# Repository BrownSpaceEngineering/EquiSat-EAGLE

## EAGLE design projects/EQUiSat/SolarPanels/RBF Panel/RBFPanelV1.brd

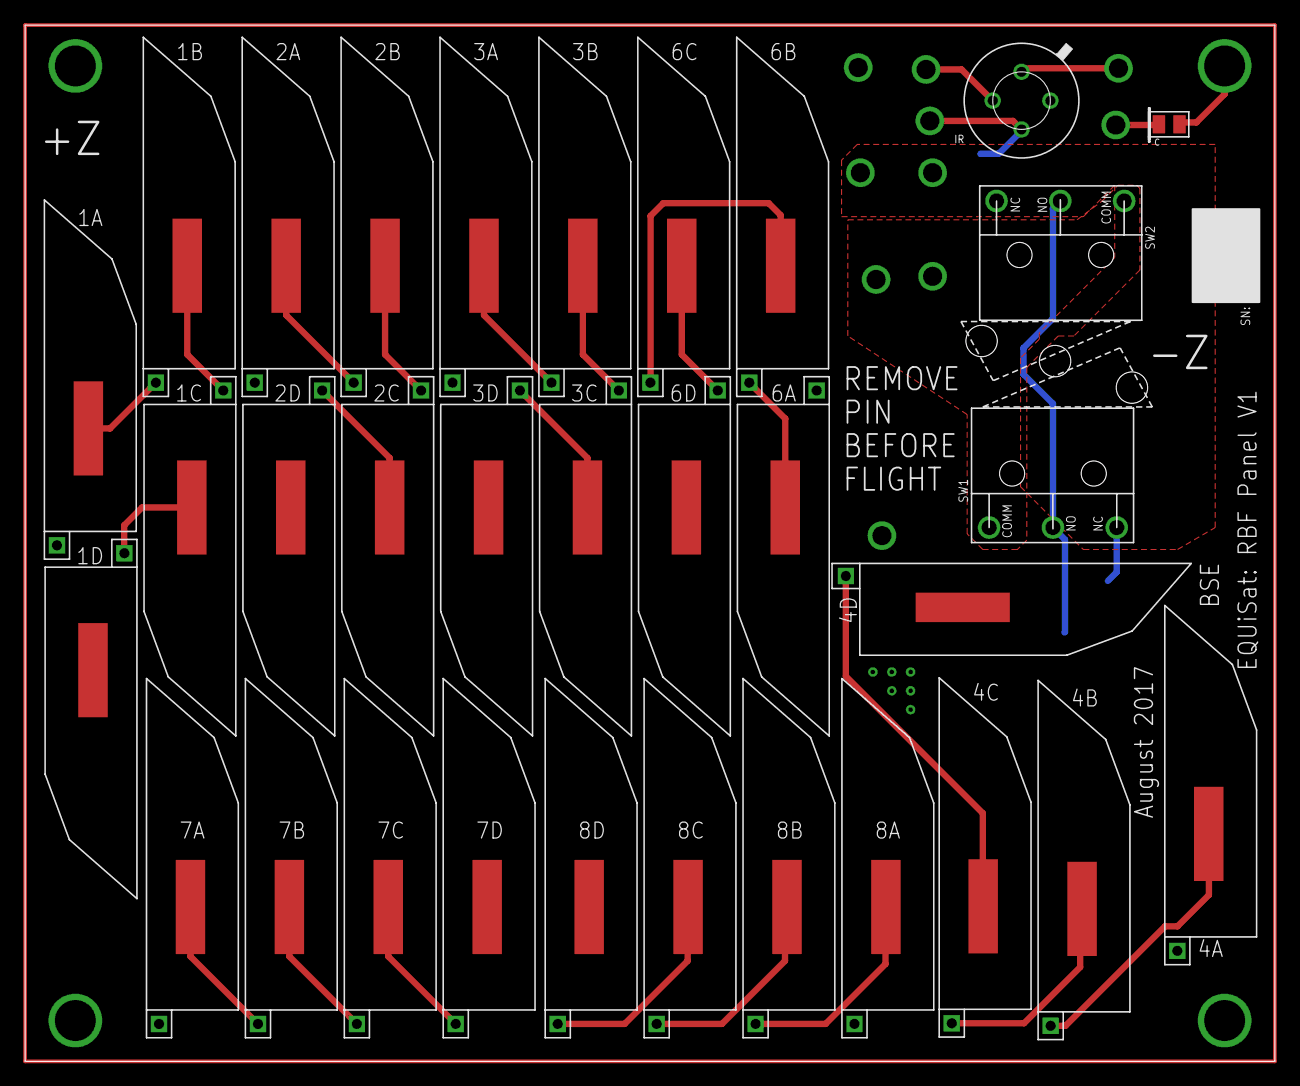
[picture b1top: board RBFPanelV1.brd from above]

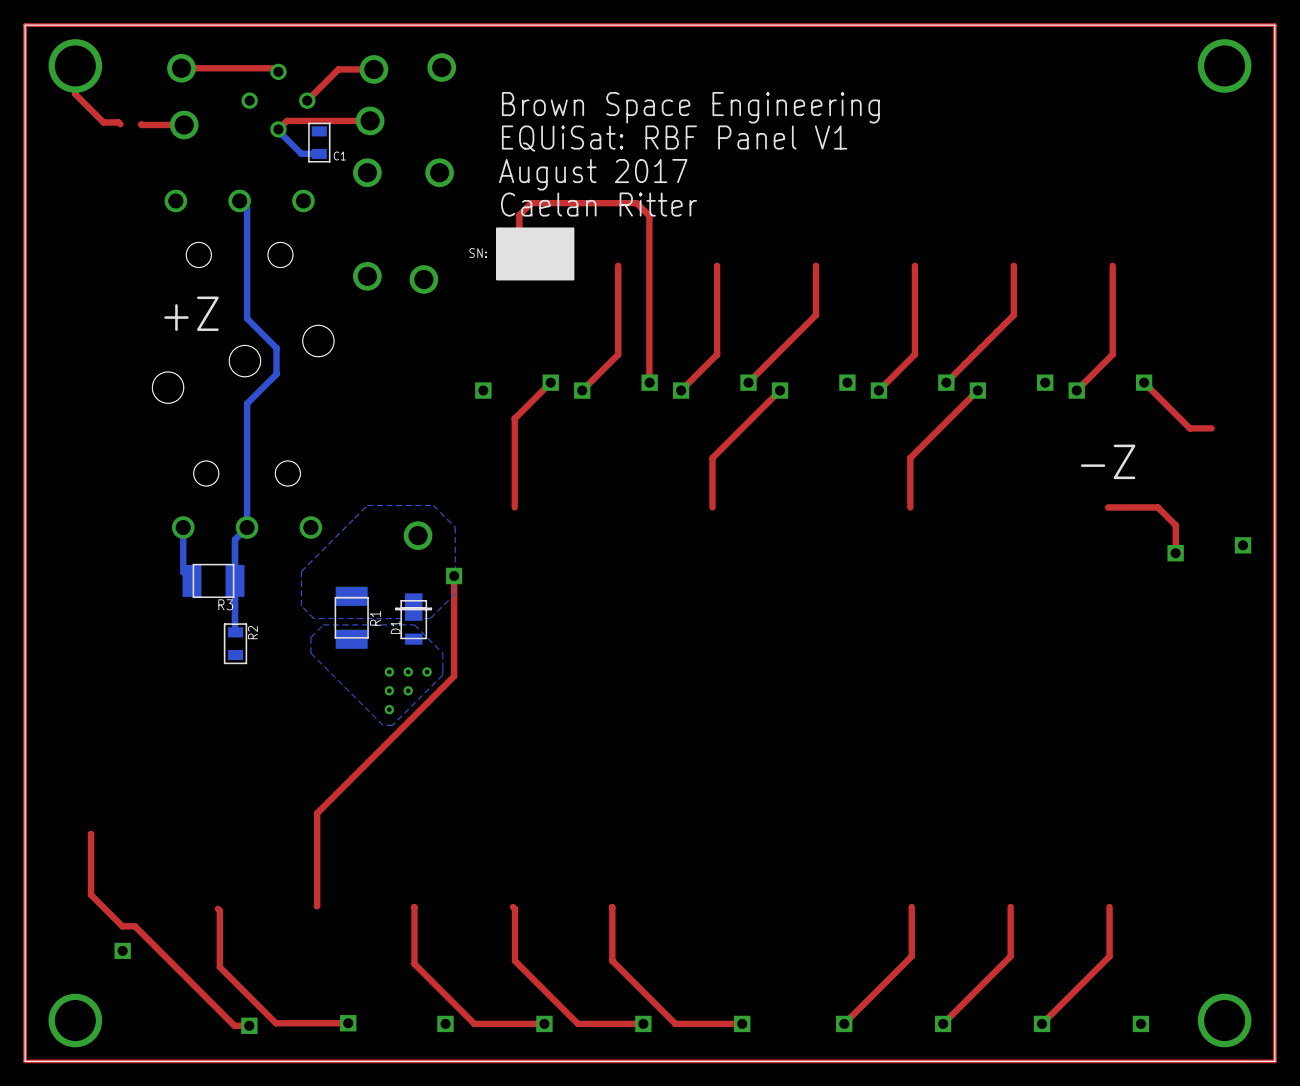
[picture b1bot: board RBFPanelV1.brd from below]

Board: 2 copper layers, 99.5 x 82.5 mm, 47 parts (5 on the bottom side), 31 nets.

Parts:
1A, 1B, 1C, 1D, 2A, 2B, 2C, 2D, 3A, 3B, 3C, 3D, 4A, 4B, 4C, 4D, 6A, 6B, 6C, 6D, 7A, 7B, 7C, 7D, 8A, 8B, 8C, 8D: SOLARCELLV3; TRISOLX-V3
3V3: 3V3; VIA-60MIL
C1: 0.1uF; 0805
D1: DFLS130L; PWRDI-123
GND: GND; VIA-60MIL
IR: MXL90620
PD: PHOTODETECTOR; PHOTODECTORDEVICE2
PD-OUT: PD-OUT; VIA-60MIL
PWR-OUT: SP-PWR-OUT; VIA-60MIL
R1, R3: 0R; 1210
R2: 10M; 0805
SCL: SCL; VIA-60MIL
SDA: SDA; VIA-60MIL
SW1, SW2: D2F-L-A
V1, V2: LION-IN; VIA-60MIL
V3, V4: LION-OUT; VIA-60MIL

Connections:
3V3: 3V3.P$1, C1.2, IR.VDD
GND: 1A.ANODE, 2A.ANODE, 3A.ANODE, 4A.ANODE, 6A.ANODE, 7A.ANODE, 8A.ANODE, C1.1, GND.P$1, IR.VSS, PD.A, R2.2
LION-IN: SW1.P$1, SW2.P$1, V1.P$1, V2.P$1
LION-OUT: R3.P$2, SW1.P$3, SW2.P$3, V3.P$1, V4.P$1
unnamed: 2C.CATHODE, 2D.ANODE
unnamed: 1C.CATHODE, 1D.ANODE
unnamed: 1B.CATHODE, 1C.ANODE
unnamed: 1A.CATHODE, 1B.ANODE
unnamed: 2B.CATHODE, 2C.ANODE
unnamed: 2A.CATHODE, 2B.ANODE
unnamed: 3C.CATHODE, 3D.ANODE
unnamed: 3B.CATHODE, 3C.ANODE
unnamed: 3A.CATHODE, 3B.ANODE
unnamed: 4C.CATHODE, 4D.ANODE
unnamed: 4B.CATHODE, 4C.ANODE
unnamed: 4A.CATHODE, 4B.ANODE
unnamed: R2.1, R3.P$1, SW1.P$2, SW2.P$2
unnamed: 6C.CATHODE, 6D.ANODE
unnamed: 6B.CATHODE, 6C.ANODE
unnamed: 6A.CATHODE, 6B.ANODE
unnamed: 7C.CATHODE, 7D.ANODE
unnamed: 7B.CATHODE, 7C.ANODE
unnamed: 7A.CATHODE, 7B.ANODE
unnamed: 8C.CATHODE, 8D.ANODE
unnamed: 8B.CATHODE, 8C.ANODE
unnamed: 8A.CATHODE, 8B.ANODE
PD-OUT: PD.C, PD-OUT.P$1
SCL: IR.SCL, SCL.P$1
SDA: IR.SDA, SDA.P$1
SP-PWR: 1D.CATHODE, 2D.CATHODE, 3D.CATHODE, 4D.CATHODE, 6D.CATHODE, 7D.CATHODE, 8D.CATHODE, D1.A, R1.P$1
SP-PWR-OUT: D1.C, PWR-OUT.P$1, R1.P$2

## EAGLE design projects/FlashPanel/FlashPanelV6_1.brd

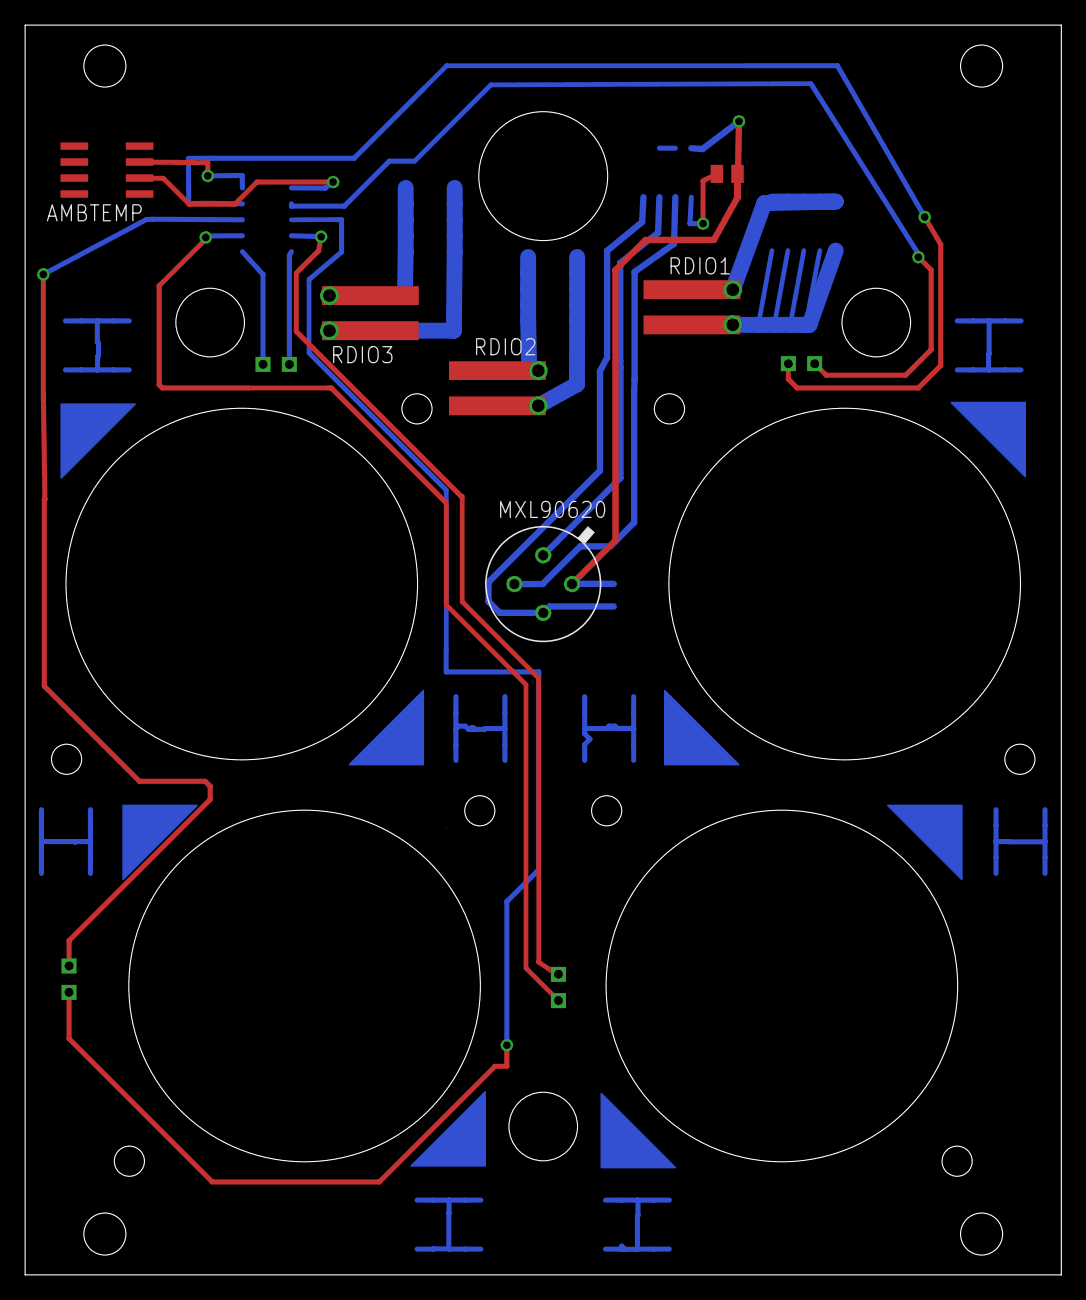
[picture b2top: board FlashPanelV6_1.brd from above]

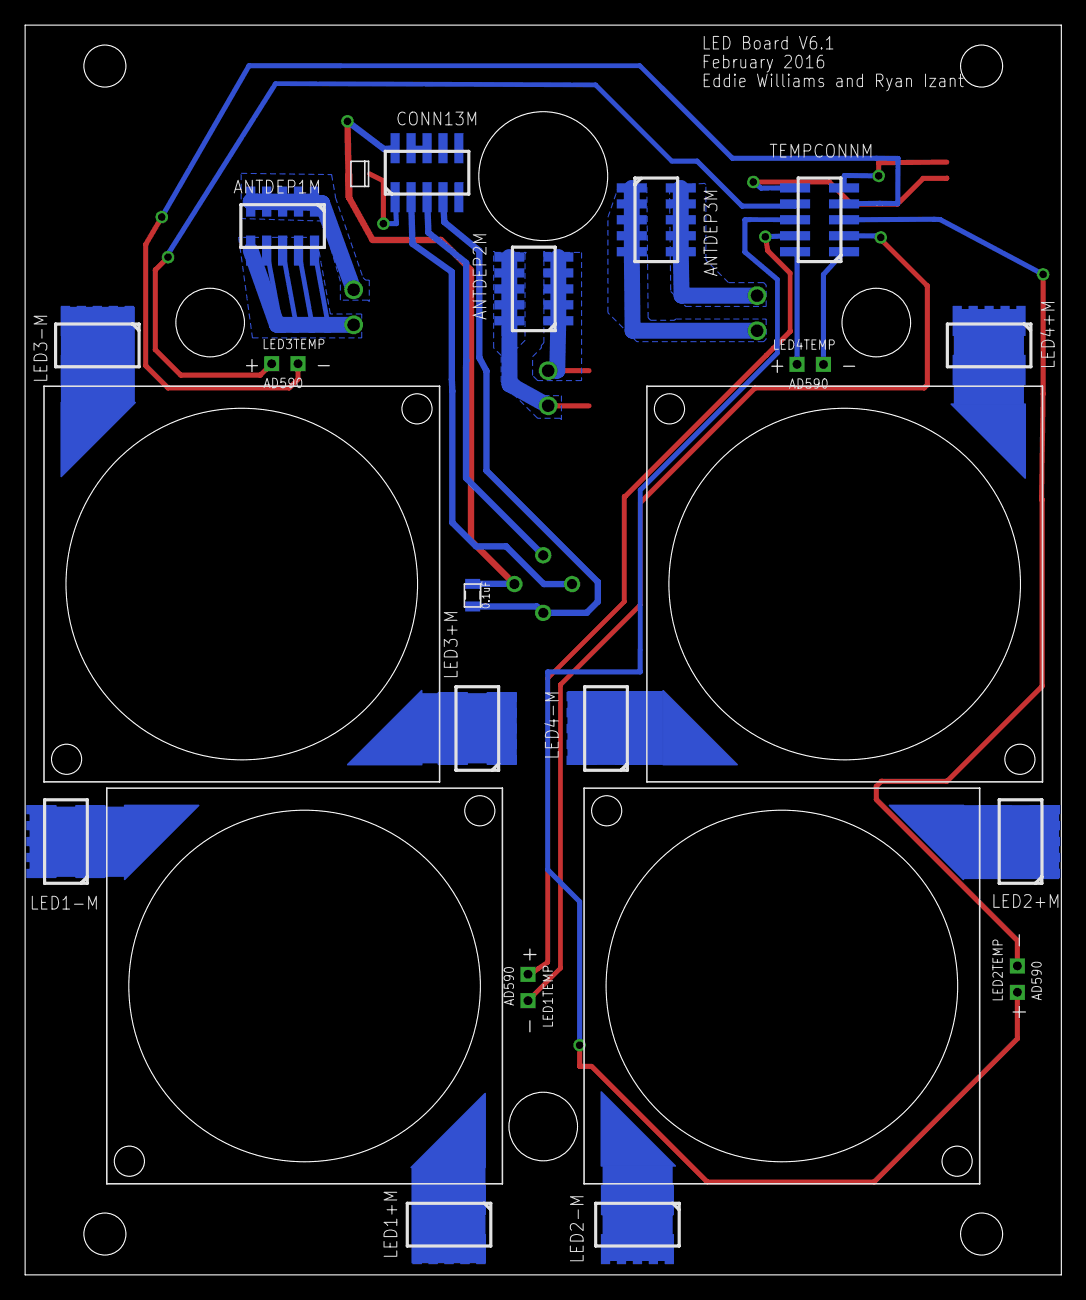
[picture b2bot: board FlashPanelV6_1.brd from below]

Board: 2 copper layers, 82.5 x 99.5 mm, 28 parts (26 on the bottom side), 30 nets.

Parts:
AMBTEMP: AD590; 8SOIC
ANTDEP1M, ANTDEP2M, ANTDEP3M: 10PINMALE
C1: 0.1uF; 0805
CONN13M: 10PINMALE
LED1, LED2, LED3, LED4: CXM27
LED1+M, LED1-M, LED2+M, LED2-M, LED3+M, LED3-M, LED4+M, LED4-M: 10PINMALE
LED1TEMP, LED2TEMP, LED3TEMP, LED4TEMP: AD590-TH; AD590TH
RDIO1, RDIO2, RDIO3: RDIO; RDIO_DPLY
TEMPCONNM: 10PINMALE
U$1: MXL90620
U$2: PHOTODETECTBOTTOM

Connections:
3V3: C1.2, CONN13M.P4, U$1.VDD
GND: C1.1, CONN13M.P10, U$1.VSS, U$2.GND
unnamed: LED3.ANODE, LED3+M.P1, LED3+M.P2, LED3+M.P3, LED3+M.P4, LED3+M.P5, LED3+M.P6, LED3+M.P7, LED3+M.P8, LED3+M.P9, LED3+M.P10
unnamed: LED3.CATHODE, LED3-M.P1, LED3-M.P2, LED3-M.P3, LED3-M.P4, LED3-M.P5, LED3-M.P6, LED3-M.P7, LED3-M.P8, LED3-M.P9, LED3-M.P10
unnamed: LED2.CATHODE, LED2+M.P1, LED2+M.P2, LED2+M.P3, LED2+M.P4, LED2+M.P5, LED2+M.P6, LED2+M.P7, LED2+M.P8, LED2+M.P9, LED2+M.P10
unnamed: LED2.ANODE, LED2-M.P1, LED2-M.P2, LED2-M.P3, LED2-M.P4, LED2-M.P5, LED2-M.P6, LED2-M.P7, LED2-M.P8, LED2-M.P9, LED2-M.P10
unnamed: LED1.CATHODE, LED1+M.P1, LED1+M.P2, LED1+M.P3, LED1+M.P4, LED1+M.P5, LED1+M.P6, LED1+M.P7, LED1+M.P8, LED1+M.P9, LED1+M.P10
unnamed: LED1.ANODE, LED1-M.P1, LED1-M.P2, LED1-M.P3, LED1-M.P4, LED1-M.P5, LED1-M.P6, LED1-M.P7, LED1-M.P8, LED1-M.P9, LED1-M.P10
unnamed: LED4.CATHODE, LED4-M.P1, LED4-M.P2, LED4-M.P3, LED4-M.P4, LED4-M.P5, LED4-M.P6, LED4-M.P7, LED4-M.P8, LED4-M.P9, LED4-M.P10
unnamed: LED4.ANODE, LED4+M.P1, LED4+M.P2, LED4+M.P3, LED4+M.P4, LED4+M.P5, LED4+M.P6, LED4+M.P7, LED4+M.P8, LED4+M.P9, LED4+M.P10
unnamed: ANTDEP1M.P1, ANTDEP1M.P2, ANTDEP1M.P3, ANTDEP1M.P4, ANTDEP1M.P5, RDIO1.P3, RDIO1.P4
unnamed: ANTDEP2M.P6, ANTDEP2M.P7, ANTDEP2M.P8, ANTDEP2M.P9, ANTDEP2M.P10, RDIO2.P1, RDIO2.P2
unnamed: ANTDEP2M.P1, ANTDEP2M.P2, ANTDEP2M.P3, ANTDEP2M.P4, ANTDEP2M.P5, RDIO2.P3, RDIO2.P4
unnamed: ANTDEP3M.P6, ANTDEP3M.P7, ANTDEP3M.P8, ANTDEP3M.P9, ANTDEP3M.P10, RDIO3.P1, RDIO3.P2
unnamed: ANTDEP3M.P1, ANTDEP3M.P2, ANTDEP3M.P3, ANTDEP3M.P4, ANTDEP3M.P5, RDIO3.P3, RDIO3.P4
unnamed: LED4TEMP.P$2, TEMPCONNM.P1
unnamed: LED1TEMP.P$2, TEMPCONNM.P2
unnamed: LED2TEMP.P$2, TEMPCONNM.P3
unnamed: LED3TEMP.P$2, TEMPCONNM.P4
unnamed: LED4TEMP.P$1, TEMPCONNM.P10
unnamed: LED1TEMP.P$1, TEMPCONNM.P9
unnamed: LED2TEMP.P$1, TEMPCONNM.P8
unnamed: LED3TEMP.P$1, TEMPCONNM.P7
unnamed: AMBTEMP.3, TEMPCONNM.P5
unnamed: AMBTEMP.2, TEMPCONNM.P6
PDOUT: CONN13M.P1, U$2.PWROUT
RDIO1: ANTDEP1M.P6, ANTDEP1M.P7, ANTDEP1M.P8, ANTDEP1M.P9, ANTDEP1M.P10, RDIO1.P1, RDIO1.P2
SCL: CONN13M.P3, U$1.SCL
SDA: CONN13M.P2, U$1.SDA
TEST: CONN13M.P8, CONN13M.P9

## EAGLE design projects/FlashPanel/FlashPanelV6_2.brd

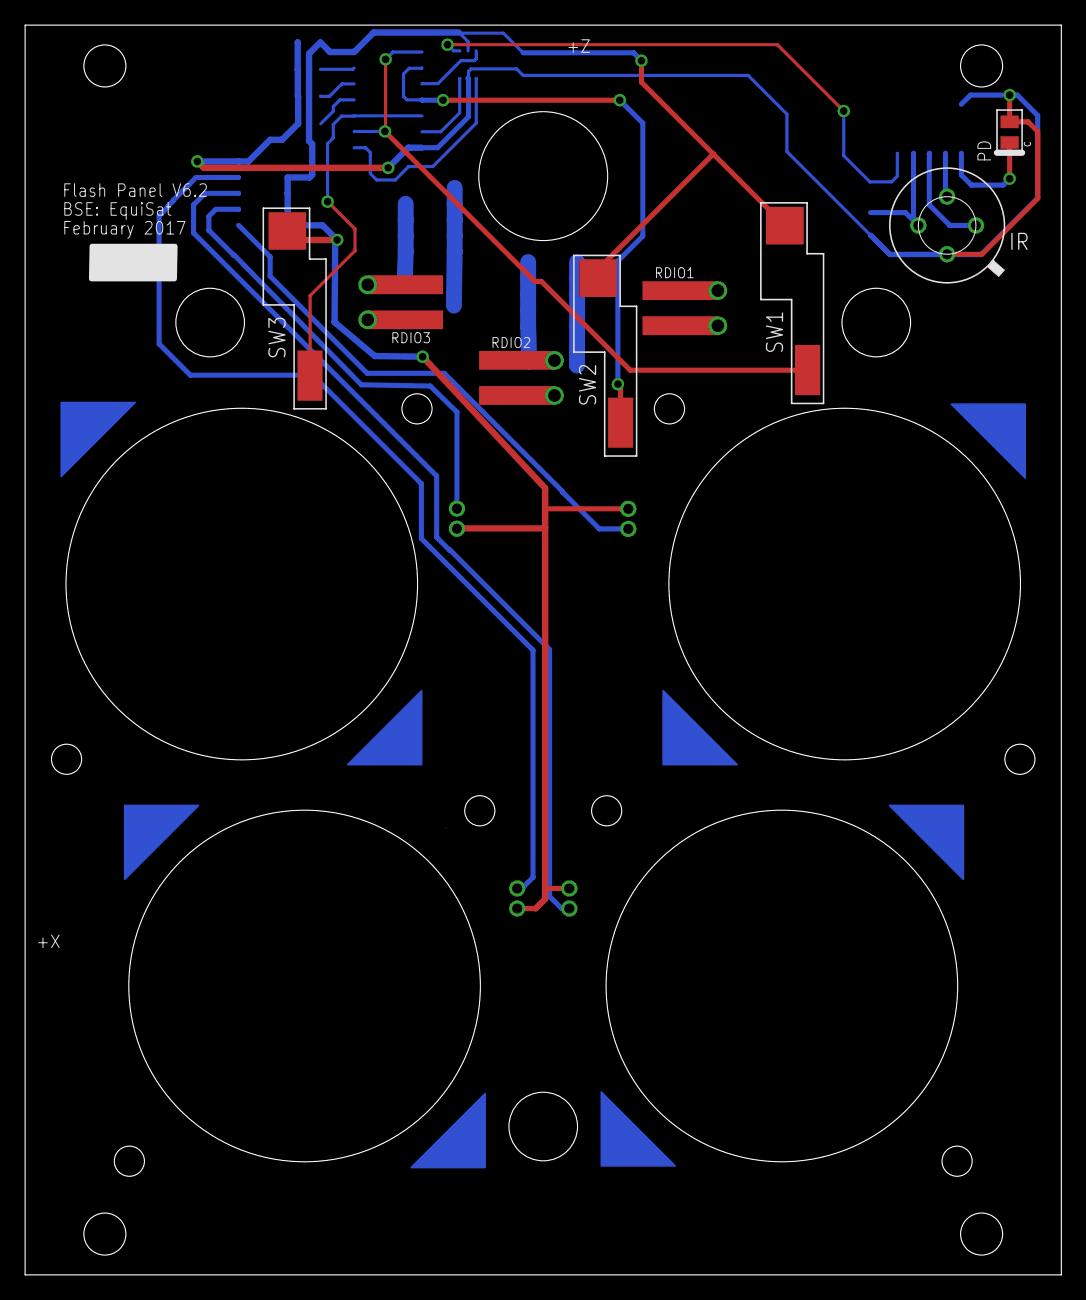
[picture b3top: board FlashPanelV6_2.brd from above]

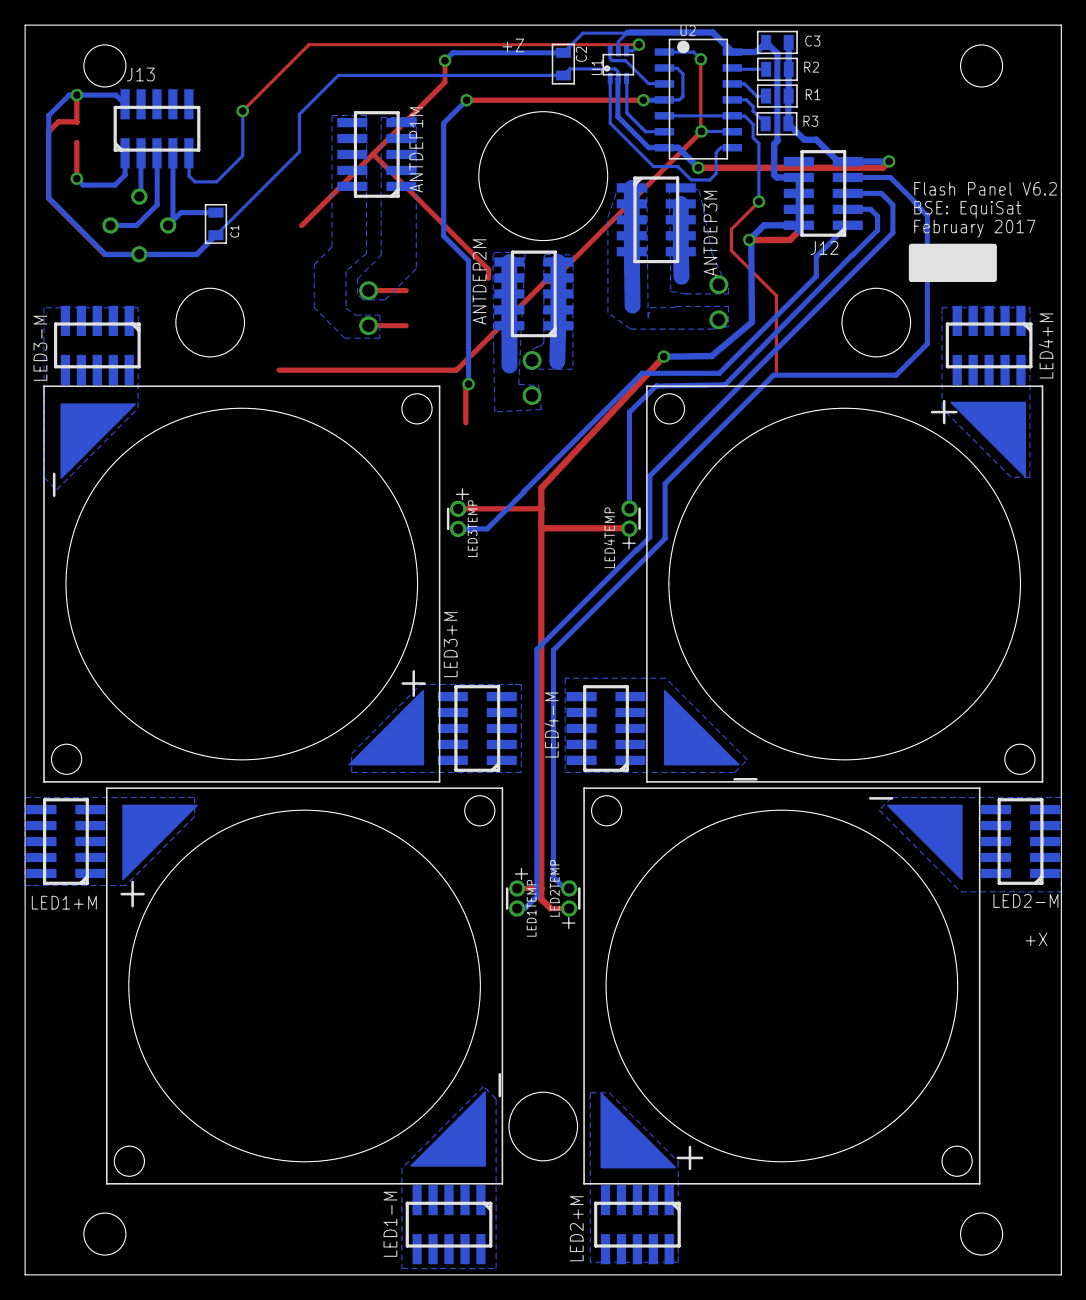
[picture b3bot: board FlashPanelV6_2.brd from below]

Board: 2 copper layers, 82.5 x 99.5 mm, 37 parts (25 on the bottom side), 34 nets.

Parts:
ANTDEP1M, ANTDEP2M, ANTDEP3M: 10PINMALE
C1, C2, C3: 0.1uF; 0805
IR: MXL90614; MXL90620
J12, J13: 10PINMALE
LED1, LED2, LED3, LED4: CXM27
LED1+M, LED1-M, LED2+M, LED2-M, LED3+M, LED3-M, LED4+M, LED4-M: 10PINMALE
LED1TEMP, LED2TEMP, LED3TEMP, LED4TEMP: AD590FLATPACK; FLATPACK
PD: TEMD6200
R1, R2, R3: 10K; 0805
RDIO1, RDIO2, RDIO3: RDIO; RDIO_DPLY
SW1, SW2, SW3: SW-DETECT; SW-SPRING
U1: SN74LVC1G332; DCK-6
U2: CD74HC08M96; SOIC-14

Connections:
5V: C2.1, C3.1, J12.P7, J12.P8, J12.P9, J12.P10, LED1TEMP.+, LED2TEMP.+, LED3TEMP.+, LED4TEMP.+, SW1.P$1, SW2.P$1, SW3.P$1, U1.P$5, U2.P$14
DET_RTN: J13.P5, U1.P$4
GND: C1.1, C2.2, C3.2, IR.VSS, J12.P5, J13.P10, PD.A, R1.1, R2.1, R3.1, U1.P$2, U2.P$7
IRVDD: C1.2, IR.VDD, J13.P4
LED1M: LED1.CATHODE, LED1-M.P1, LED1-M.P2, LED1-M.P3, LED1-M.P4, LED1-M.P5, LED1-M.P6, LED1-M.P7, LED1-M.P8, LED1-M.P9, LED1-M.P10
LED1P: LED1.ANODE, LED1+M.P1, LED1+M.P2, LED1+M.P3, LED1+M.P4, LED1+M.P5, LED1+M.P6, LED1+M.P7, LED1+M.P8, LED1+M.P9, LED1+M.P10
LED1TEMP-: J12.P3, LED1TEMP.-
LED2M: LED2.CATHODE, LED2-M.P1, LED2-M.P2, LED2-M.P3, LED2-M.P4, LED2-M.P5, LED2-M.P6, LED2-M.P7, LED2-M.P8, LED2-M.P9, LED2-M.P10
LED2P: LED2.ANODE, LED2+M.P1, LED2+M.P2, LED2+M.P3, LED2+M.P4, LED2+M.P5, LED2+M.P6, LED2+M.P7, LED2+M.P8, LED2+M.P9, LED2+M.P10
LED2TEMP-: J12.P4, LED2TEMP.-
LED3M: LED3.CATHODE, LED3-M.P1, LED3-M.P2, LED3-M.P3, LED3-M.P4, LED3-M.P5, LED3-M.P6, LED3-M.P7, LED3-M.P8, LED3-M.P9, LED3-M.P10
LED3P: LED3.ANODE, LED3+M.P1, LED3+M.P2, LED3+M.P3, LED3+M.P4, LED3+M.P5, LED3+M.P6, LED3+M.P7, LED3+M.P8, LED3+M.P9, LED3+M.P10
LED3TEMP-: J12.P1, LED3TEMP.-
LED4M: LED4.CATHODE, LED4-M.P1, LED4-M.P2, LED4-M.P3, LED4-M.P4, LED4-M.P5, LED4-M.P6, LED4-M.P7, LED4-M.P8, LED4-M.P9, LED4-M.P10
LED4P: LED4.ANODE, LED4+M.P1, LED4+M.P2, LED4+M.P3, LED4+M.P4, LED4+M.P5, LED4+M.P6, LED4+M.P7, LED4+M.P8, LED4+M.P9, LED4+M.P10
LED4TEMP-: J12.P2, LED4TEMP.-
unnamed: U1.P$6, U2.P$3
unnamed: U1.P$3, U2.P$6
unnamed: U1.P$1, U2.P$8
unnamed: SW1.P$2, U2.P$1, U2.P$9
unnamed: SW2.P$2, U2.P$2, U2.P$4
unnamed: SW3.P$2, U2.P$5, U2.P$10
unnamed: R2.2, U2.P$13
unnamed: R1.2, U2.P$12
unnamed: R3.2, U2.P$11
PDOUT: J13.P1, PD.C
RDIO1+: ANTDEP1M.P6, ANTDEP1M.P7, ANTDEP1M.P8, ANTDEP1M.P9, ANTDEP1M.P10, RDIO1.P3, RDIO1.P4
RDIO1-: ANTDEP1M.P1, ANTDEP1M.P2, ANTDEP1M.P3, ANTDEP1M.P4, ANTDEP1M.P5, RDIO1.P1, RDIO1.P2
RDIO2+: ANTDEP2M.P6, ANTDEP2M.P7, ANTDEP2M.P8, ANTDEP2M.P9, ANTDEP2M.P10, RDIO2.P3, RDIO2.P4
RDIO2-: ANTDEP2M.P1, ANTDEP2M.P2, ANTDEP2M.P3, ANTDEP2M.P4, ANTDEP2M.P5, RDIO2.P1, RDIO2.P2
RDIO3+: ANTDEP3M.P6, ANTDEP3M.P7, ANTDEP3M.P8, ANTDEP3M.P9, ANTDEP3M.P10, RDIO3.P3, RDIO3.P4
RDIO3-: ANTDEP3M.P1, ANTDEP3M.P2, ANTDEP3M.P3, ANTDEP3M.P4, ANTDEP3M.P5, RDIO3.P1, RDIO3.P2
SCL: IR.SCL, J13.P3
SDA: IR.SDA, J13.P2

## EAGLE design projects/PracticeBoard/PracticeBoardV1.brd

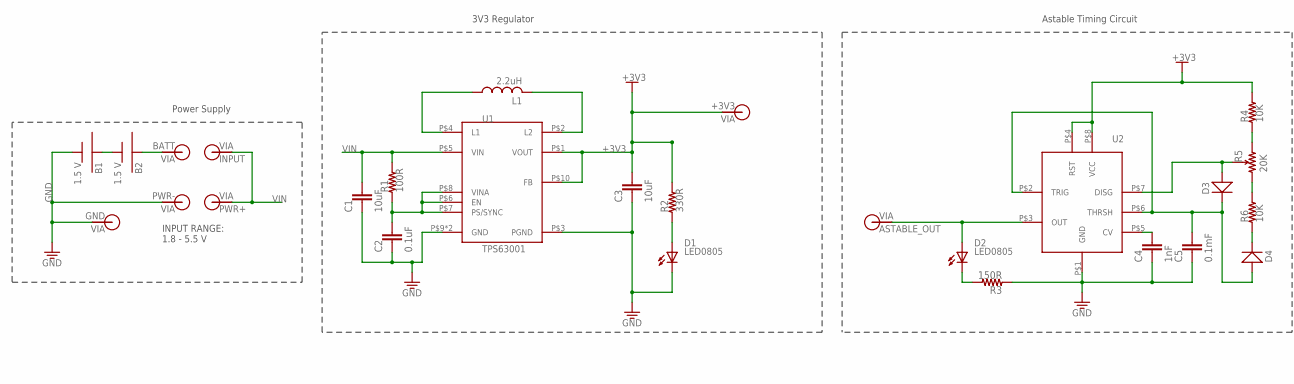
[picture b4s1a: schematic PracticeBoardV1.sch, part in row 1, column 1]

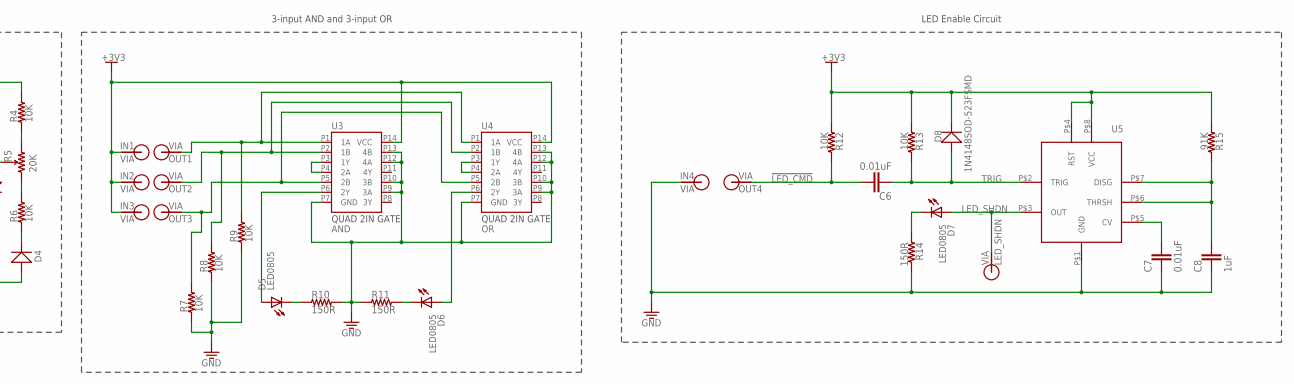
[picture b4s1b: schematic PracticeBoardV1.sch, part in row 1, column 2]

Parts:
B1, B2: 1.5 V; BCAAPC-BATT-HOLDER
C1, C3: 10uF; 0805
C2: 0.1uF; 0805
C4: 1nF; 0805
C5: 0.1mF; 0805
C6, C7: 0.01uF; 0805
C8: 1uF; 0805
D1, D2, D5, D6, D7: LED0805; 0805-D
D3, D4: 1N4148THRU-HOLE; 1N4148
D8: 1N4148SOD-523FSMD; SOD-523F
L1: 2.2uH; L3225M
R1: 100R; 0805
R2: 330R; 0805
R3, R10, R11, R14: 150R; 0805
R4, R6, R7, R8, R9, R12, R13: 10K; 0805
R5: 20K; P160KN
R15: 91K; 0805
U1: TPS63001; QFN10_POWERPAD
U2, U5: TLC555; SO-8
U3: AND; VQFN-14
U4: OR; TSSOP-14
V1: BATT; VIA-60MIL-SQ
V2: PWR-; VIA-60MIL-SQ
V3: INPUT; VIA-60MIL-SQ
V4: PWR+; VIA-60MIL-SQ
V5: +3V3; VIA-60MIL-SQ
V6: ASTABLE_OUT; VIA-60MIL-SQ
V7: IN1; VIA-60MIL-SQ
V8: IN2; VIA-60MIL-SQ
V9: IN3; VIA-60MIL-SQ
V10: OUT1; VIA-60MIL-SQ
V11: OUT2; VIA-60MIL-SQ
V12: OUT3; VIA-60MIL-SQ
V13: IN4; VIA-60MIL-SQ
V14: OUT4; VIA-60MIL-SQ
V15: LED_SHDN; VIA-60MIL-SQ
V16: GND; VIA-60MIL-SQ

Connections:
!LED_CMD!: C6.1, R12.2, V14.P$1
+3V3: C3.1, D8.C, R2.2, R4.2, R12.1, R13.1, R15.1, U1.P$1 (VOUT), U1.P$10 (FB), U2.P$4 (RST), U2.P$8 (VCC), U3.P14 (VCC), U4.P14 (VCC), U5.P$4 (RST), U5.P$8 (VCC), V5.P$1, V7.P$1, V8.P$1, V9.P$1
ASTABLE_OUT: D2.A, U2.P$3 (OUT), V6.P$1
GND: B1.MINUS, C1.2, C2.2, C3.2, C4.2, C5.2, C7.2, C8.2, D1.C, R3.1, R7.1, R8.1, R9.1, R10.2, R11.1, R14.2, U1.P$3 (PGND), U1.P$9 (GND), U1.PAD (GND), U2.P$1 (GND), U3.P7 (GND), U3.P9 (3A), U3.P10 (3B), U3.P12 (4A), U3.P13 (4B), U4.P7 (GND), U4.P9 (3A), U4.P10 (3B), U4.P12 (4A), U4.P13 (4B), U5.P$1 (GND), V2.P$1, V13.P$1, V16.P$1
LED_SHDN: D7.A, U5.P$3 (OUT), V15.P$1
unnamed: B1.PLUS, B2.MINUS
unnamed: C4.1, U2.P$5 (CV)
unnamed: C5.1, D3.C, D4.A, U2.P$2 (TRIG), U2.P$6 (THRSH)
unnamed: D5.C, R10.1
unnamed: L1.1, U1.P$4 (L1)
unnamed: L1.2, U1.P$2 (L2)
unnamed: R4.1, R5.P2 (2)
unnamed: D6.C, R11.2
unnamed: C2.1, R1.1, U1.P$6 (EN), U1.P$7 (PS/SYNC), U1.P$8 (VINA)
unnamed: R9.2, U3.P1 (1A), U4.P1 (1A), V10.P$1
unnamed: R8.2, U3.P2 (1B), U4.P2 (1B), V11.P$1
unnamed: R7.2, U3.P5 (2B), U4.P5 (2B), V12.P$1
unnamed: U4.P3 (1Y), U4.P4 (2A)
unnamed: U3.P3 (1Y), U3.P4 (2A)
unnamed: B2.PLUS, V1.P$1
unnamed: D3.A, R5.P3, U2.P$7 (DISG)
unnamed: R5.P1 (1), R6.2
unnamed: D7.C, R14.1
unnamed: C8.1, R15.2, U5.P$6 (THRSH), U5.P$7 (DISG)
unnamed: D5.A, U3.P6 (2Y)
unnamed: D2.C, R3.2
unnamed: C7.1, U5.P$5 (CV)
unnamed: D6.A, U4.P6 (2Y)
unnamed: D4.C, R6.1
unnamed: D1.A, R2.1
TRIG: C6.2, D8.A, R13.2, U5.P$2 (TRIG)
VIN: C1.1, R1.2, U1.P$5 (VIN), V3.P$1, V4.P$1

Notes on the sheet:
3V3 Regulator
Astable Timing Circuit
3-input AND and 3-input OR
LED Enable Circuit
Power Supply
INPUT RANGE: 1.8 - 5.5 V

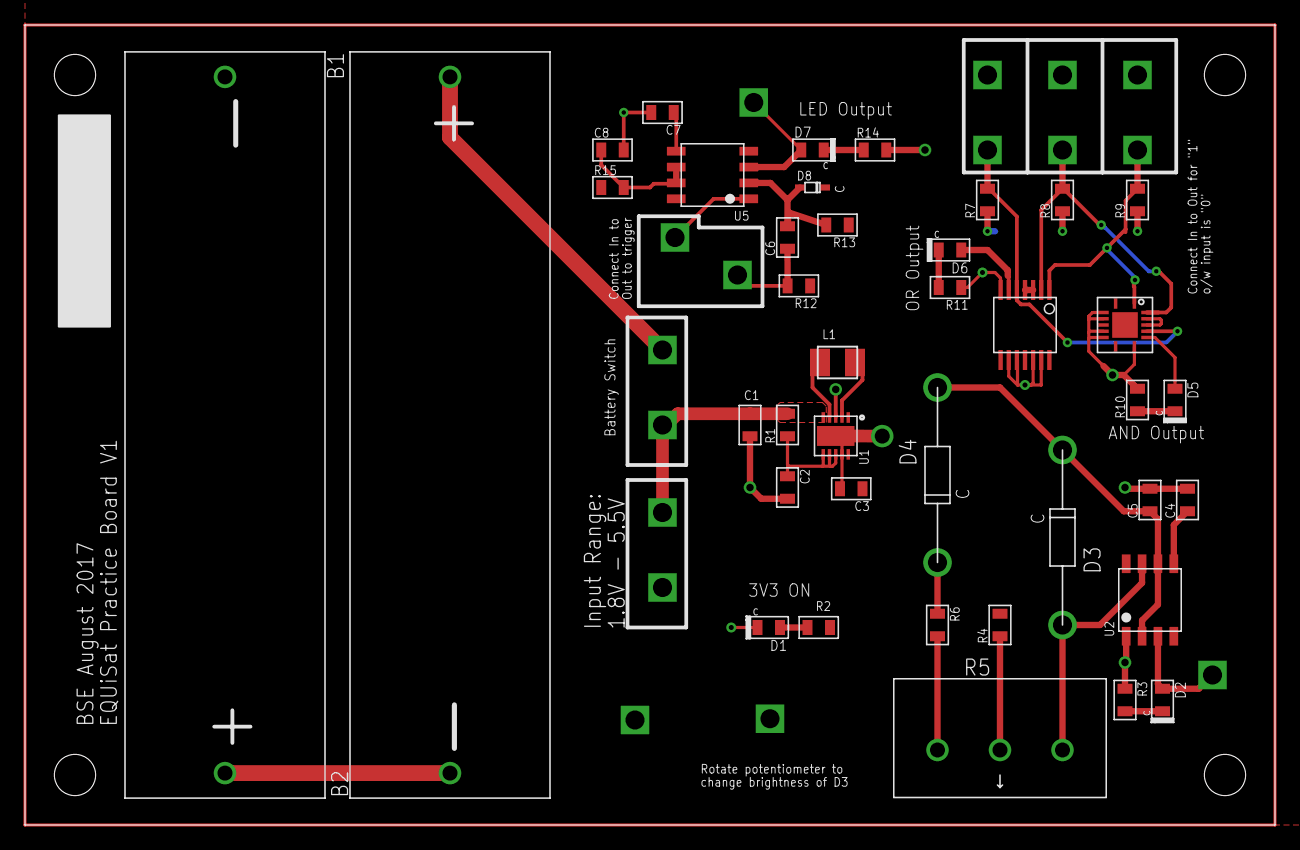
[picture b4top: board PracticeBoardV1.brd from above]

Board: 2 copper layers, 100.0 x 64.0 mm, 55 parts (0 on the bottom side), 32 nets.

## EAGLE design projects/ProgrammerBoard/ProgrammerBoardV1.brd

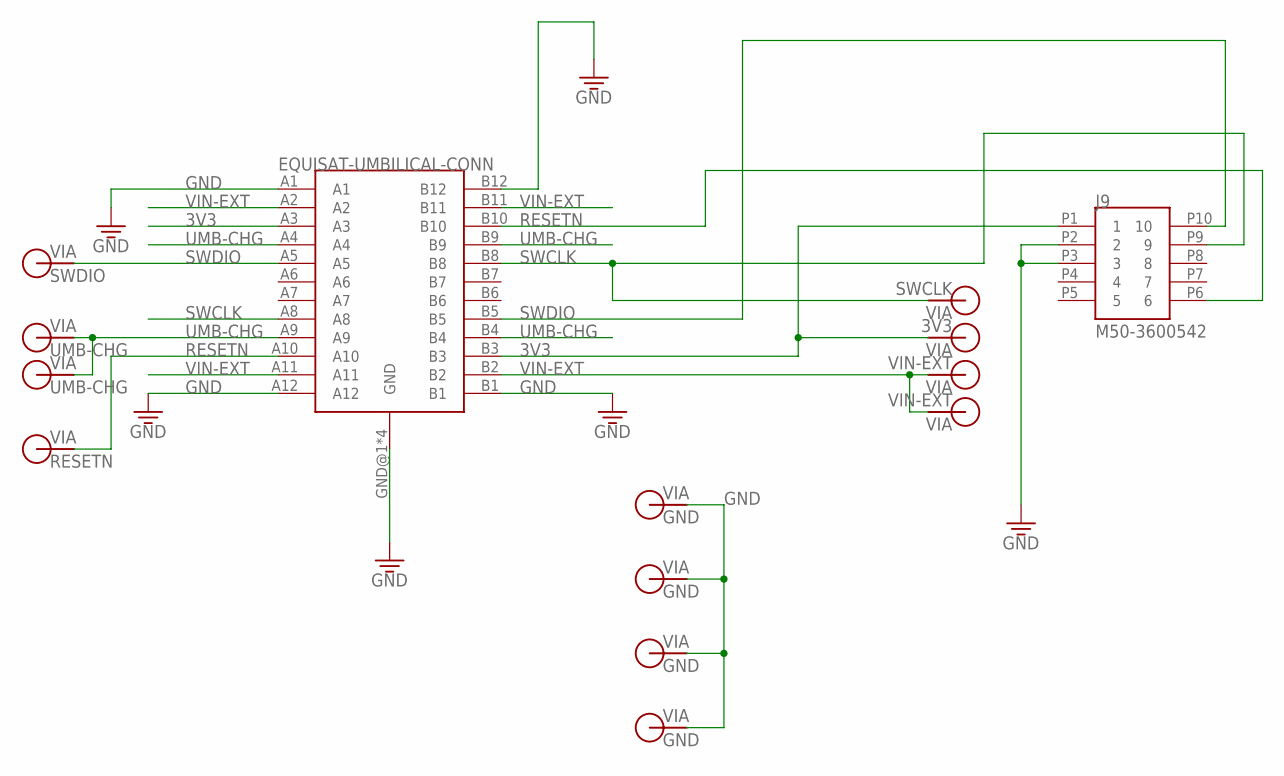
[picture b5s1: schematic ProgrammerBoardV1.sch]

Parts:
J9: M50-3600542; 10PINMALE
U$1: EQUISAT-UMBILICAL-CONN; USB-C-RCPT-SMT
V1, V2, V3, V4: GND; VIA-60MIL
V5: SWDIO; VIA-60MIL
V6, V7: UMB-CHG; VIA-60MIL
V8: RESETN; VIA-60MIL
V9: SWCLK; VIA-60MIL
V10: 3V3; VIA-60MIL
V11, V12: VIN-EXT; VIA-60MIL

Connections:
3V3: J9.P1 (1), U$1.A3, U$1.B3, V10.P$1
GND: J9.P2 (2), J9.P3 (3), U$1.A1, U$1.A12, U$1.B1, U$1.B12, U$1.GND@1 (GND), U$1.GND@2 (GND), U$1.GND@3 (GND), U$1.GND@4 (GND), V1.P$1, V2.P$1, V3.P$1, V4.P$1
RESETN: J9.P6 (6), U$1.A10, U$1.B10, V8.P$1
SWCLK: J9.P9 (9), U$1.A8, U$1.B8, V9.P$1
SWDIO: J9.P10 (10), U$1.A5, U$1.B5, V5.P$1
UMB-CHG: U$1.A4, U$1.A9, U$1.B4, U$1.B9, V6.P$1, V7.P$1
VIN-EXT: U$1.A2, U$1.A11, U$1.B2, U$1.B11, V11.P$1, V12.P$1

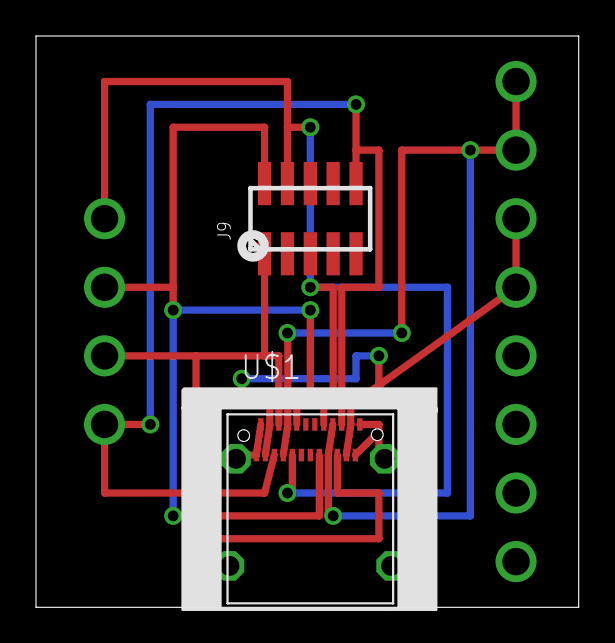
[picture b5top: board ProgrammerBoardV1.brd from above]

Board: 2 copper layers, 30.1 x 31.7 mm, 14 parts (0 on the bottom side), 7 nets.

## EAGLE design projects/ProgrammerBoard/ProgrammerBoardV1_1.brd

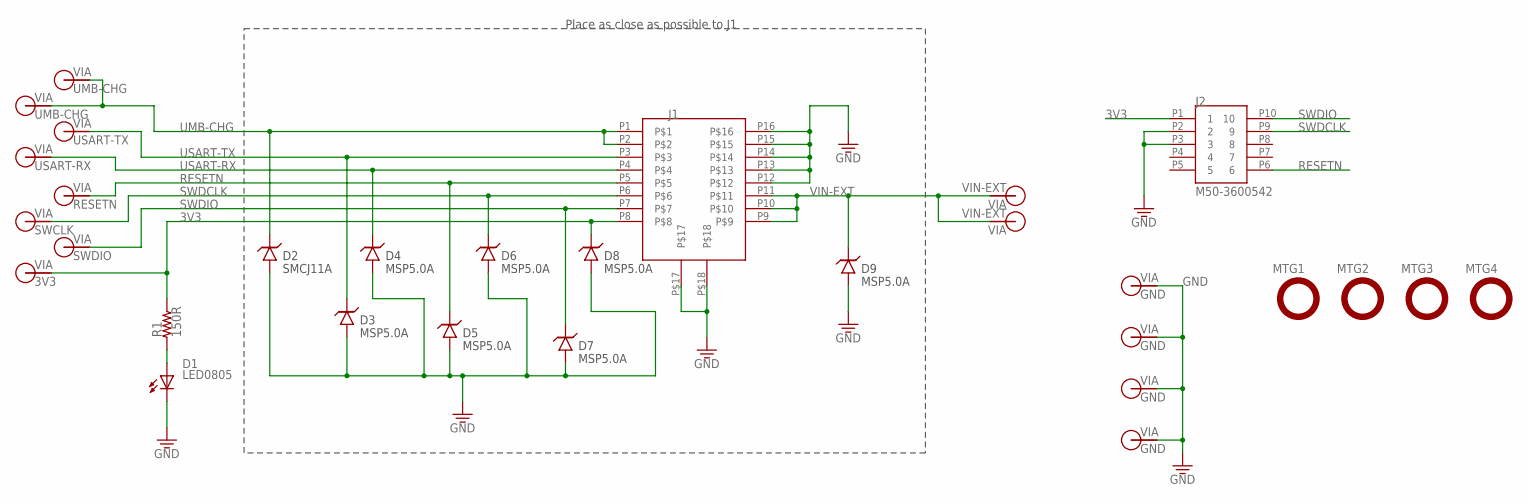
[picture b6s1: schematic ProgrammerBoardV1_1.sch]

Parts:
D1: LED0805; 0805-D
D2: SMCJ11A; DO-214AB
D3, D4, D5, D6, D7, D8, D9: MSP5.0A; MICROSMP
J1: FFC-16REVERSE; 68611614422-REVERSE
J2: M50-3600542; 10PINMALE
MTG1, MTG2, MTG3, MTG4: MTG-NPTH-M2; M2-NPTH
R1: 150R; 0805
V1, V2, V3, V4: GND; VIA-60MIL
V5: SWDIO; VIA-60MIL
V6, V7: UMB-CHG; VIA-60MIL
V8: RESETN; VIA-60MIL
V9: SWCLK; VIA-60MIL
V10: 3V3; VIA-60MIL
V11, V12: VIN-EXT; VIA-60MIL
V13: USART-RX; VIA-60MIL
V14: USART-TX; VIA-60MIL

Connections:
3V3: D8.C, J1.P8, J2.P1 (1), R1.2, V10.P$1
GND: D1.C, D2.A, D3.A, D4.A, D5.A, D6.A, D7.A, D8.A, D9.A, J1.P12, J1.P13, J1.P14, J1.P15, J1.P16, J1.P$17, J1.P$18, J2.P2 (2), J2.P3 (3), V1.P$1, V2.P$1, V3.P$1, V4.P$1
unnamed: D1.A, R1.1
RESETN: D5.C, J1.P5, J2.P6 (6), V8.P$1
SWDCLK: D6.C, J1.P6, J2.P9 (9), V9.P$1
SWDIO: D7.C, J1.P7, J2.P10 (10), V5.P$1
UMB-CHG: D2.C, J1.P1, J1.P2, V6.P$1, V7.P$1
USART-RX: D4.C, J1.P4, V13.P$1
USART-TX: D3.C, J1.P3, V14.P$1
VIN-EXT: D9.C, J1.P9, J1.P10, J1.P11, V11.P$1, V12.P$1

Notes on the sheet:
Place as close as possible to J1

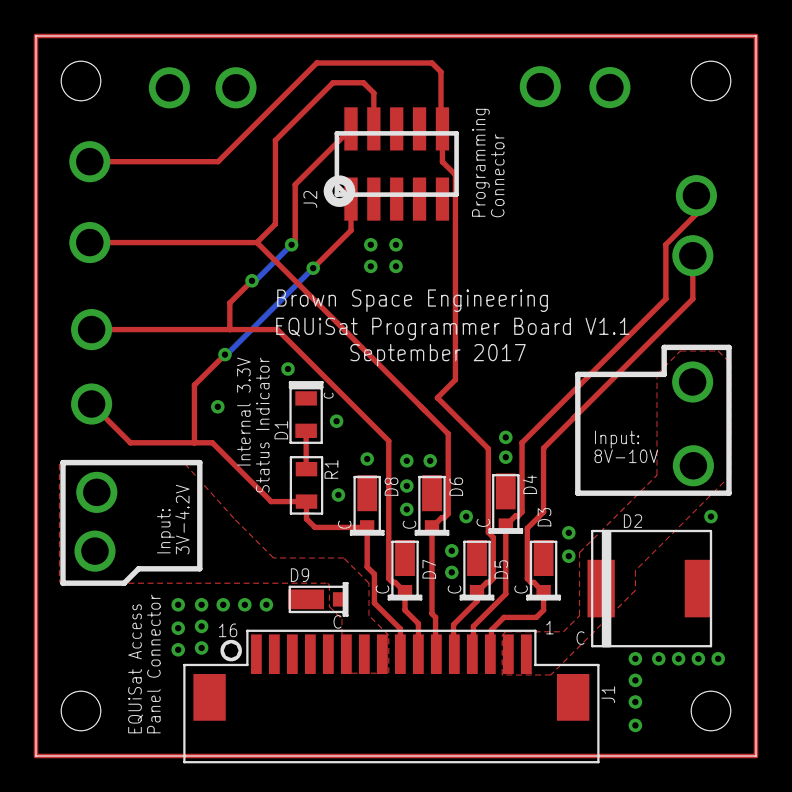
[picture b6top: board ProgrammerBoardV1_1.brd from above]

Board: 2 copper layers, 40.0 x 40.0 mm, 30 parts (0 on the bottom side), 10 nets.
